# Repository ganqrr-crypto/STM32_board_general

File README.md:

This project is a STM32 dev board i am making it to get more integrated into the STM ecosystem and see many other chips how work... 
It is a general STM32 board and here is how is structured:

It has obviously some schematics and a PCB and here is the BOM:

BOM

Here are some immages of the proejct

one is schematic and one is PCB. I made this projet a 2 layer PCB.

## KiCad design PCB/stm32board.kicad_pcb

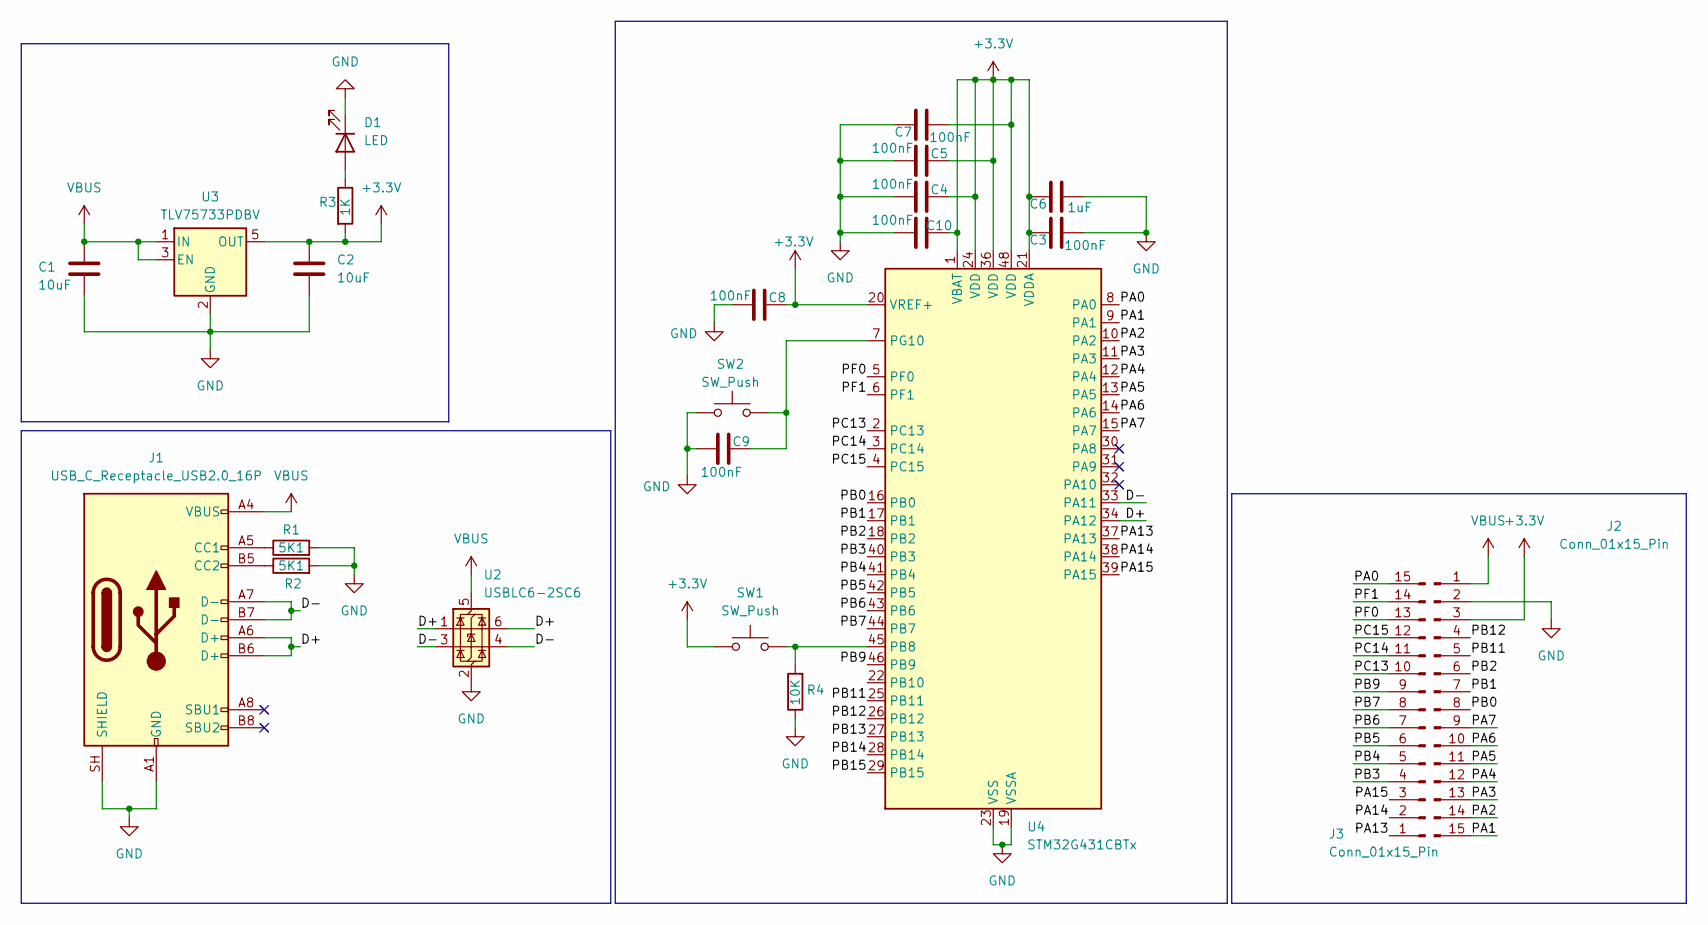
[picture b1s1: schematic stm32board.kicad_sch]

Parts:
C1, C2: 10uF; C_0603_1608Metric_Pad1.08x0.95mm_HandSolder
C3, C4, C5, C7, C8, C9, C10: 100nF; C_0603_1608Metric_Pad1.08x0.95mm_HandSolder
C6: 1uF; C_0603_1608Metric_Pad1.08x0.95mm_HandSolder
D1: LED; LED_0603_1608Metric_Pad1.05x0.95mm_HandSolder
J1: USB_C_Receptacle_USB2.0_16P; USB_C_Receptacle_GCT_USB4105-xx-A_16P_TopMnt_Horizontal
J2, J3: Conn_01x15_Pin; PinHeader_1x15_P2.54mm_Vertical
R1, R2: 5K1; C_0603_1608Metric_Pad1.08x0.95mm_HandSolder
R3: 1K; C_0603_1608Metric_Pad1.08x0.95mm_HandSolder
R4: 10K; C_0603_1608Metric_Pad1.08x0.95mm_HandSolder
SW1, SW2: SW_Push; SW_SPST_PTS810
U2: USBLC6-2SC6; SOT-23-6
U3: TLV75733PDBV; SOT-23-5
U4: STM32G431CBTx; LQFP-48_7x7mm_P0.5mm

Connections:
+3.3V: C2.1, C3.2, C4.2, C5.2, C6.2, C7.1, C8.2, C10.2, J2.3, R3.2, SW1.1, U3.5 (OUT), U4.1 (VBAT), U4.20 (VREF+), U4.21 (VDDA), U4.24 (VDD), U4.36 (VDD), U4.48 (VDD)
/D+: J1.A6 (D+), J1.B6 (D+), U2.1 (I/O1), U2.6 (I/O1), U4.34 (PA12)
/D-: J1.A7 (D-), J1.B7 (D-), U2.3 (I/O2), U2.4 (I/O2), U4.33 (PA11)
/PA0: J3.15, U4.8 (PA0)
/PA1: J2.15, U4.9 (PA1)
/PA2: J2.14, U4.10 (PA2)
/PA3: J2.13, U4.11 (PA3)
/PA4: J2.12, U4.12 (PA4)
/PA5: J2.11, U4.13 (PA5)
/PA6: J2.10, U4.14 (PA6)
/PA7: J2.9, U4.15 (PA7)
/PA13: J3.1, U4.37 (PA13)
/PA14: J3.2, U4.38 (PA14)
/PA15: J3.3, U4.39 (PA15)
/PB0: J2.8, U4.16 (PB0)
/PB1: J2.7, U4.17 (PB1)
/PB2: J2.6, U4.18 (PB2)
/PB3: J3.4, U4.40 (PB3)
/PB4: J3.5, U4.41 (PB4)
/PB5: J3.6, U4.42 (PB5)
/PB6: J3.7, U4.43 (PB6)
/PB7: J3.8, U4.44 (PB7)
/PB9: J3.9, U4.46 (PB9)
/PB11: J2.5, U4.25 (PB11)
/PB12: J2.4, U4.26 (PB12)
/PB13: U4.27 (PB13)
/PB14: U4.28 (PB14)
/PB15: U4.29 (PB15)
/PC13: J3.10, U4.2 (PC13)
/PC14: J3.11, U4.3 (PC14)
/PC15: J3.12, U4.4 (PC15)
/PF0: J3.13, U4.5 (PF0)
/PF1: J3.14, U4.6 (PF1)
GND: C1.2, C2.2, C3.1, C4.1, C5.1, C6.1, C7.2, C8.1, C9.1, C10.1, D1.1 (K), J1.A1 (GND), J1.A12 (GND), J1.B1 (GND), J1.B12 (GND), J1.SH (SHIELD), J2.2, R1.2, R2.2, R4.1, SW2.1, U2.2 (GND), U3.2 (GND), U4.19 (VSSA), U4.23 (VSS), U4.35 (VSS), U4.47 (VSS)
unnamed: D1.2 (A), R3.1
unnamed: J1.A5 (CC1), R1.1
unnamed: J1.B5 (CC2), R2.1
unnamed: R4.2, SW1.2, U4.45 (PB8)
unnamed: C9.2, SW2.2, U4.7 (PG10)
VBUS: C1.1, J1.A4 (VBUS), J1.A9 (VBUS), J1.B4 (VBUS), J1.B9 (VBUS), J2.1, U2.5 (VBUS), U3.1 (IN), U3.3 (EN)

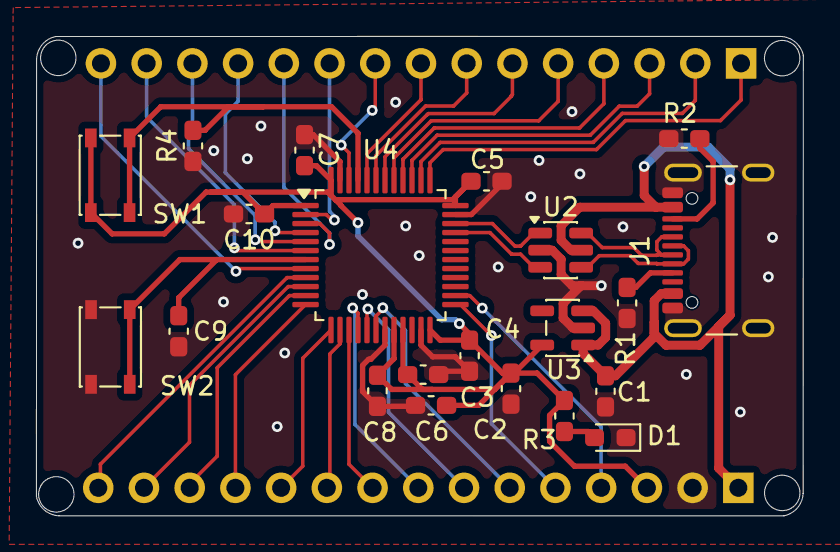
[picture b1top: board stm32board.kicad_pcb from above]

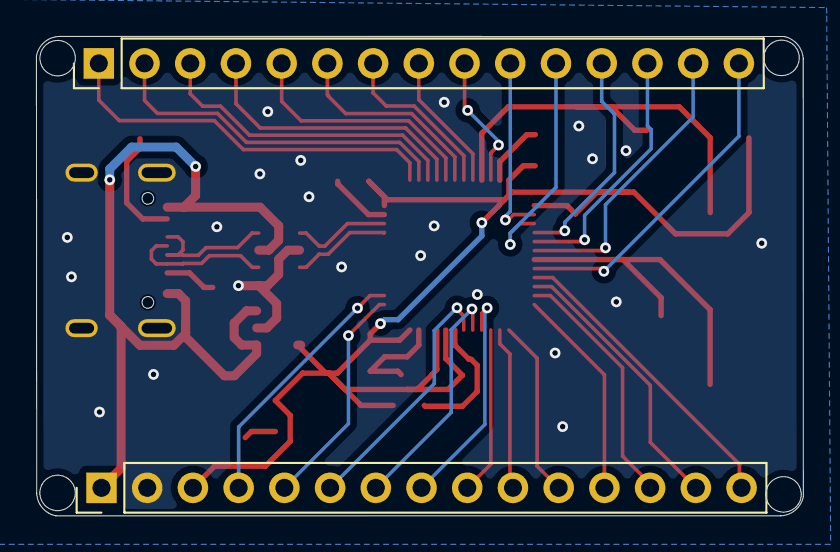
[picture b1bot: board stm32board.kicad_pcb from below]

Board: 2 copper layers, 42.6 x 26.6 mm, 23 parts (2 on the bottom side), 37 nets.
